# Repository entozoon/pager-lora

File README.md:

# Pager Lora

## Ingredients

- Arduino / ESP8266 ?
  Arduino is more conservative but doesn't seem to be the popular choice. I mean, speed might be an issue with transmission so bang it out on a Wemos with WIFI disabled.

## Goals

- Clamshell
- Nokia 5110 screen / e-ink
- Buzz tune on receipt
- Opening wakes up device screen
- Small as poss, but poss 18520 batteries, so..
- Lora communication over 300m

## Input

Mobile keypad text is a fun way to go. Revive that old skill.

### Drawing?

Would be nice, but bandwidth is limited, as well as rendering capabilities so.. it'd be a whole thing. Couldn't be real-time.. but still an option if I make a larger device.

## Comms

| Send Device      |       Listen Device        |        User |
| ---------------- | :------------------------: | ----------: |
| Listening always |      Listening always      |             |
|                  |                            |             |
| Emit (n?)        |                            |        Send |
|                  |          Receive           |        Buzz |
|                  |      Store to EEPROM       |             |
|                  | Emit message received? meh |             |
| Stop emitting    |                            |             |
|                  | Screen on, display message | Open device |
|                  |                            |             |

## Power

The power concerns are real. So let's make sure to do all dis:

### Disable WIFI on microcontroller

`WiFi.mode(WIFI_OFF);`

### Sleep

If possible, I mean perhaps it could sleep half the time? Let's have a shufty at some power requirements. Complete conjecture, but anyways:

- Microcontroller
  General: 20mA ESP w/out WIFI or 5mA for pro mini
  Sleep: Negligible

- LoRa (3.3v)
  Receiver: ≦ 10mA (LnaBoost off, band 1)
  Transmit: ≦ 120mA (+ 20dBm)
  Sleep: Negligible
  Total, if listening always and transmitting like 1% of the time: 11mA

- Screen
  Unlit: 1mA
  Backlit: <= 80mA, so maybe don't bother!

- 18650 2400mah 3.7v
  5v converters are supposedly 90% efficient so 2160mAh

So, assuming they're always listening and transmit at glorious 28.8kbps modem style speed now and then:

    Battery capacity (mA/h) / Current draw (mA) = hours of battery life  .. right?

    2160mAh / 32mA = 67 hours
    900mAh / 32mA = 28 hours
    240mAh / 32mA = 7.5 hours

Woah. I mean, these are conservative numbers too. Not three bad.
So yeah, sleep both chips if possible when closed and poss use an Arduino (5mA).

### C rating?

Literally anything is fine.
Peak current, with lit screen and full transmit is like 220mA, so 0.5C @ 500mA is enough. (18650 are 1C)

### Sleep LoRa chip

Just a reminder to sleep this along with the microcontroller.

## Battery

5V step ups bitch out under .5v, which won't matter much, but the efficiency varies with input voltage (and current): http://www.hobbytronics.co.uk/u1v10f5-5v-regulator

| Battery      |    V |  mAh | Effic | ->~mAh | Life(h) mAh/32mA | Notes                      |
| ------------ | ---: | ---: | ----: | -----: | ---------------: | -------------------------- |
| AAA (r/c)    | 1.5v | 1000 |  @70% |    700 |               22 |                            |
| AAA (r/c) x2 | 1.5v | 2000 |  @70% |   1400 |               44 |                            |
| AA (r/c)     | 1.5v | 2400 |  @70% |   1680 |               53 |                            |
| Lipo 50x30mm | 3.7v | 2000 |  @90% |   1800 |               56 | Better form factor than AA |
| 18650        | 3.7v | 2400 |  @90% |   2160 |               66 | All lipos easy to charge   |
| Lipo 90x60mm | 3.7v | 4000 |  @90% |   3600 |              113 | Phone bat size, affordable |

Lipo batteries supposedly self-disarge at only 5%/month (despite my experience), not far off alkaline.
So any lipo really, high mAh as possible for the best form factor.
But deeefinitely invest in a voltmeter setup (see below). Perhaps flash the screen hard and/or chirp for a turn off.

## Battery monitoring

Feed battery into analogue input, with a voltage divider to reduce it.

Wemos A0 has a voltage divider built in. 220k / 100k (2/3rdsness).
People say it has a range of 3.3V, but I should test that.

    +++++++++
        |
      [10k]
        |
        |----(100pF -> 1nF)---> analogue input
        |    reduce wobble? Didn't work..
        |
      [10k]
        |
    ---------

    V divideness = (R1 / R1 + R2)
                 = 1 / 2

So if my lipo spits out a mad 4.6V, A0 would receive 2.3V.
Update: 1024 max value is 6.1V, in reality, through my divider.

| Lipo V | Desc   | Dividered | A0 (theory) | Human  |
| ------ | ------ | --------: | ----------: | ------ |
| 4.6    | Pumped |       2.3 |         713 | 100%   |
| 4.2    | Full   |       2.1 |         652 | 100%   |
| 4      | Good   |         2 |         621 | 75%    |
| 3.86   | Mid    |      1.93 |         599 | 50%    |
| 3.75   | Low    |     1.875 |         582 | 20% !  |
| 3.7    | Low    |      1.85 |         574 | 10% !  |
| 3.5    | Dead   |      1.75 |         543 | 0% off |

    A0 (theory) = Dividered V / 3.3 * 1024

Empirical realities are close but a little different:

| Lipo V | Desc   | A0 (theory) | Human  |
| ------ | ------ | ----------: | ------ |
| 4.6    | Pumped |         762 | 100%   |
| 4.2    | Full   |         706 | 100%   |
| 4      | Good   |         660 | 75%    |
| 3.86   | Mid    |         634 | 50%    |
| 3.75   | Low    |         615 | 20% !  |
| 3.7    | Low    |         608 | 10% !  |
| 3.5    | Dead   |         577 | 0% off |

## Power off

It really should power itself off, LoRa et al, with low batt for safety. Might not be worth it though, I mean, do my charge protection circuits handle that? Probs eh?

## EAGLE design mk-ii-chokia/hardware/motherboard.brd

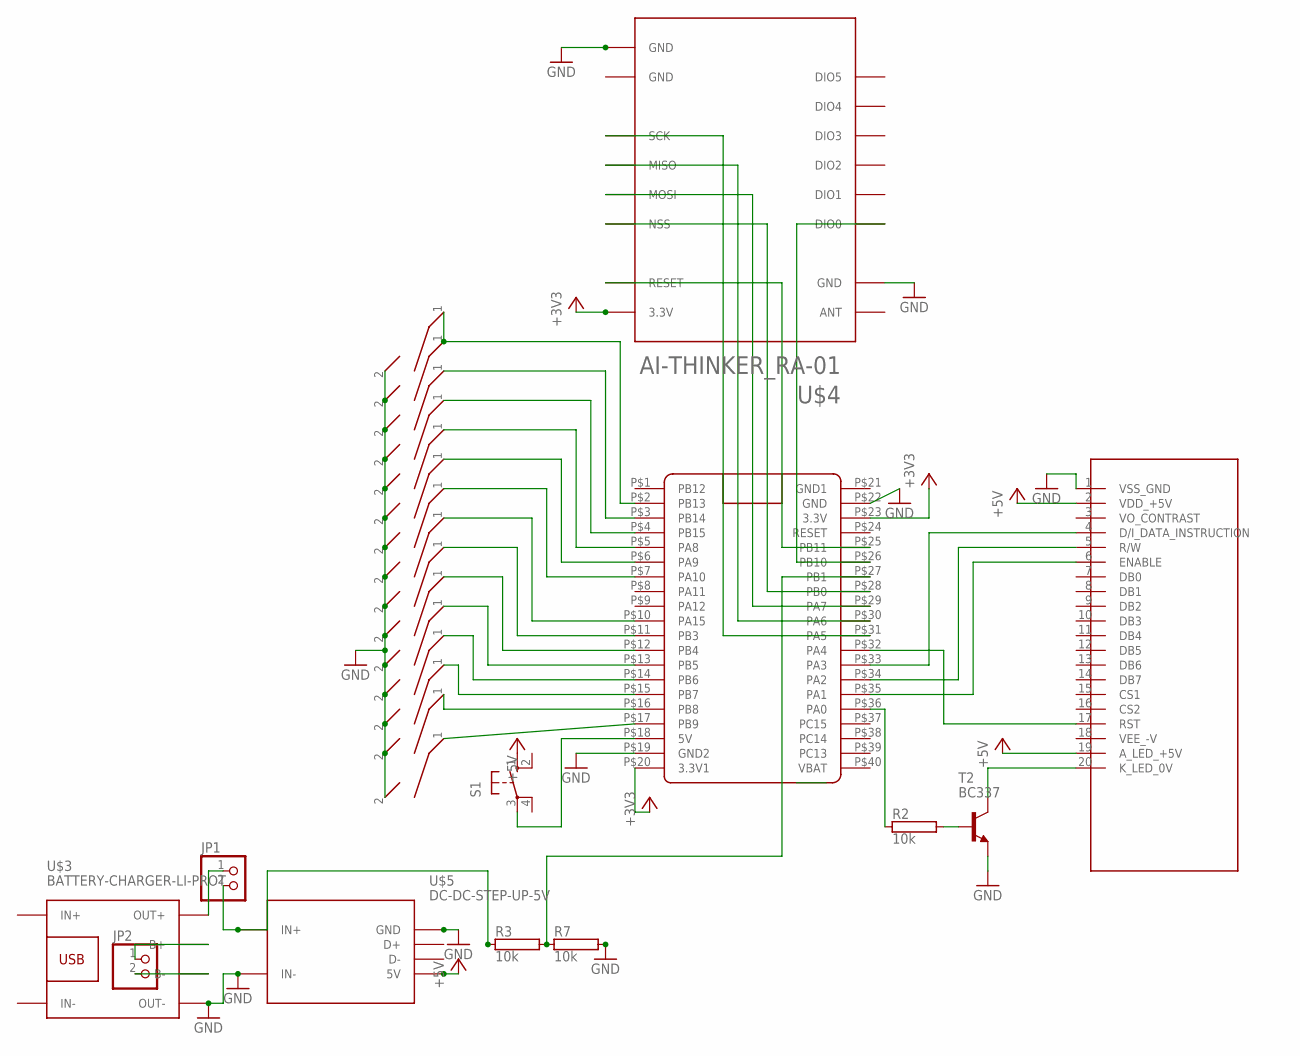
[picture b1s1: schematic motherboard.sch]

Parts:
JP1, JP2: PINHD-1X2/90; 1X02/90
R2, R3, R7: 10k; AC01
S1: 10-XX; B3F-10XX
SW1, SW2, SW3, SW4, SW5, SW6, SW7, SW8, SW9, SW10, SW11, SW12, SW13, SW14, SW15: CHERRY_MX; MX1A-XXNN
T2: BC337; TO92
U$1: W12864
U$2: BLUE_PILL
U$3: BATTERY-CHARGER-LI-PROT
U$4: AI-THINKER_RA-01
U$5: DC-DC-STEP-UP-5V

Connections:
+3V3: U$2.P$20 (3.3V1), U$2.P$23 (3.3V), U$4.P$3 (3.3V)
+5V: S1.1 (S), U$1.2 (VDD_+5V), U$1.19 (A_LED_+5V), U$5.5V
GND: R7.2, SW1.2, SW2.2, SW3.2, SW4.2, SW5.2, SW6.2, SW7.2, SW8.2, SW9.2, SW10.2, SW11.2, SW12.2, SW13.2, SW14.2, SW15.2, T2.1 (E), U$1.1 (VSS_GND), U$2.P$19 (GND2), U$2.P$22 (GND), U$3.OUT-, U$4.P$2 (GND), U$4.P$16 (GND), U$5.GND, U$5.IN-
GND1: U$2.P$21 (GND1)
unnamed: JP1.1, U$3.OUT+
unnamed: U$2.P$25 (PB11), U$4.P$4 (RESET)
unnamed: U$2.P$28 (PB0), U$4.P$15 (NSS)
unnamed: U$2.P$29 (PA7), U$4.P$14 (MOSI)
unnamed: U$2.P$30 (PA6), U$4.P$13 (MISO)
unnamed: U$2.P$31 (PA5), U$4.P$12 (SCK)
unnamed: U$2.P$26 (PB10), U$4.P$5 (DIO0)
unnamed: U$1.6 (ENABLE), U$2.P$35 (PA1)
unnamed: U$1.5 (R/W), U$2.P$34 (PA2)
unnamed: U$1.17 (RST), U$2.P$32 (PA4)
unnamed: U$1.4 (D/I_DATA_INSTRUCTION), U$2.P$33 (PA3)
unnamed: R2.2, T2.2 (B)
unnamed: T2.3 (C), U$1.20 (K_LED_0V)
unnamed: SW1.1, U$2.P$17 (PB9)
unnamed: JP1.2, R3.1, U$5.IN+
unnamed: SW2.1, U$2.P$16 (PB8)
unnamed: R2.1, U$2.P$36 (PA0)
unnamed: SW3.1, U$2.P$15 (PB7)
unnamed: SW4.1, U$2.P$14 (PB6)
unnamed: SW5.1, U$2.P$13 (PB5)
unnamed: SW6.1, U$2.P$12 (PB4)
unnamed: SW7.1, U$2.P$11 (PB3)
unnamed: R3.2, R7.1, U$2.P$27 (PB1)
unnamed: SW8.1, U$2.P$10 (PA15)
unnamed: SW9.1, U$2.P$7 (PA10)
unnamed: SW10.1, U$2.P$6 (PA9)
unnamed: SW13.1, U$2.P$3 (PB14)
unnamed: SW14.1, SW15.1, U$2.P$2 (PB13)
unnamed: SW11.1, U$2.P$5 (PA8)
unnamed: SW12.1, U$2.P$4 (PB15)
unnamed: JP2.1, U$3.B+
unnamed: JP2.2, U$3.B-
unnamed: S1.3, U$2.P$18 (5V)

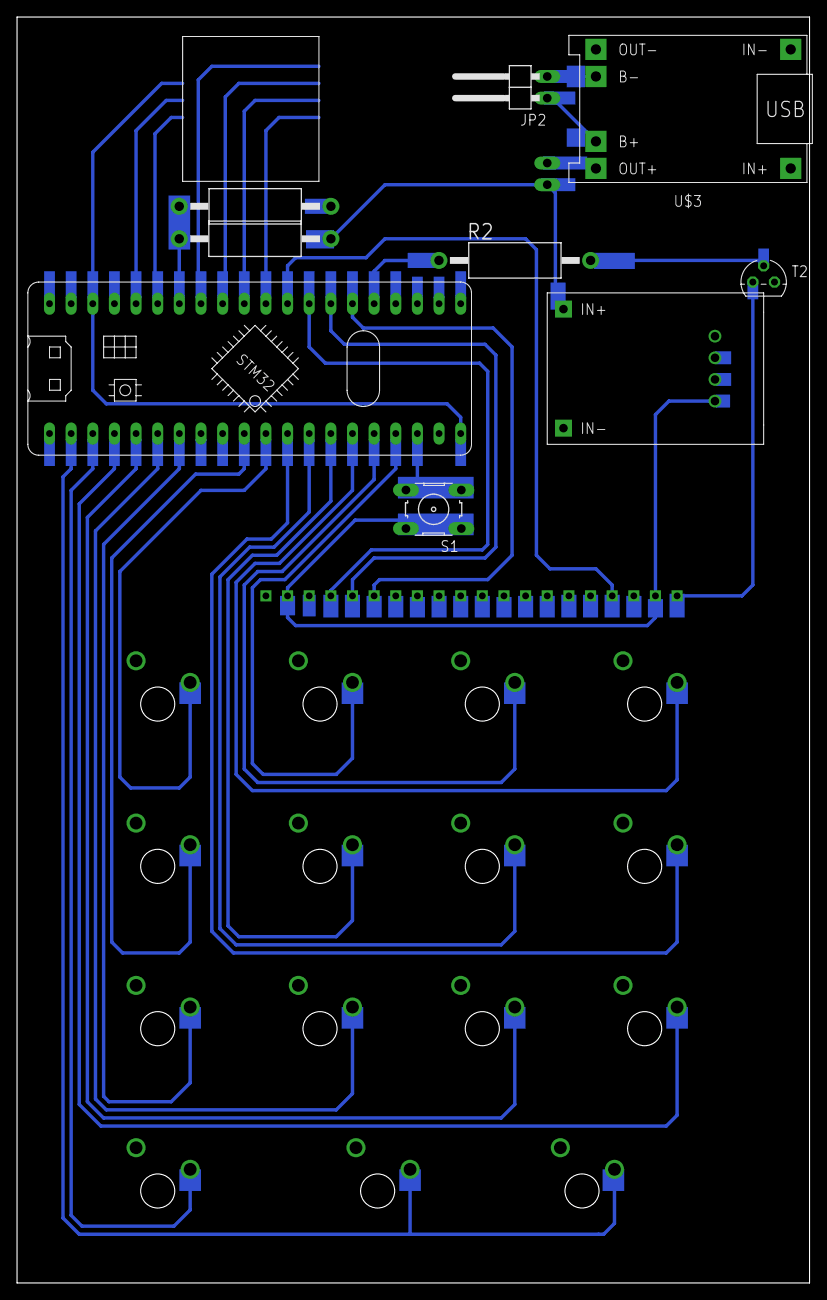
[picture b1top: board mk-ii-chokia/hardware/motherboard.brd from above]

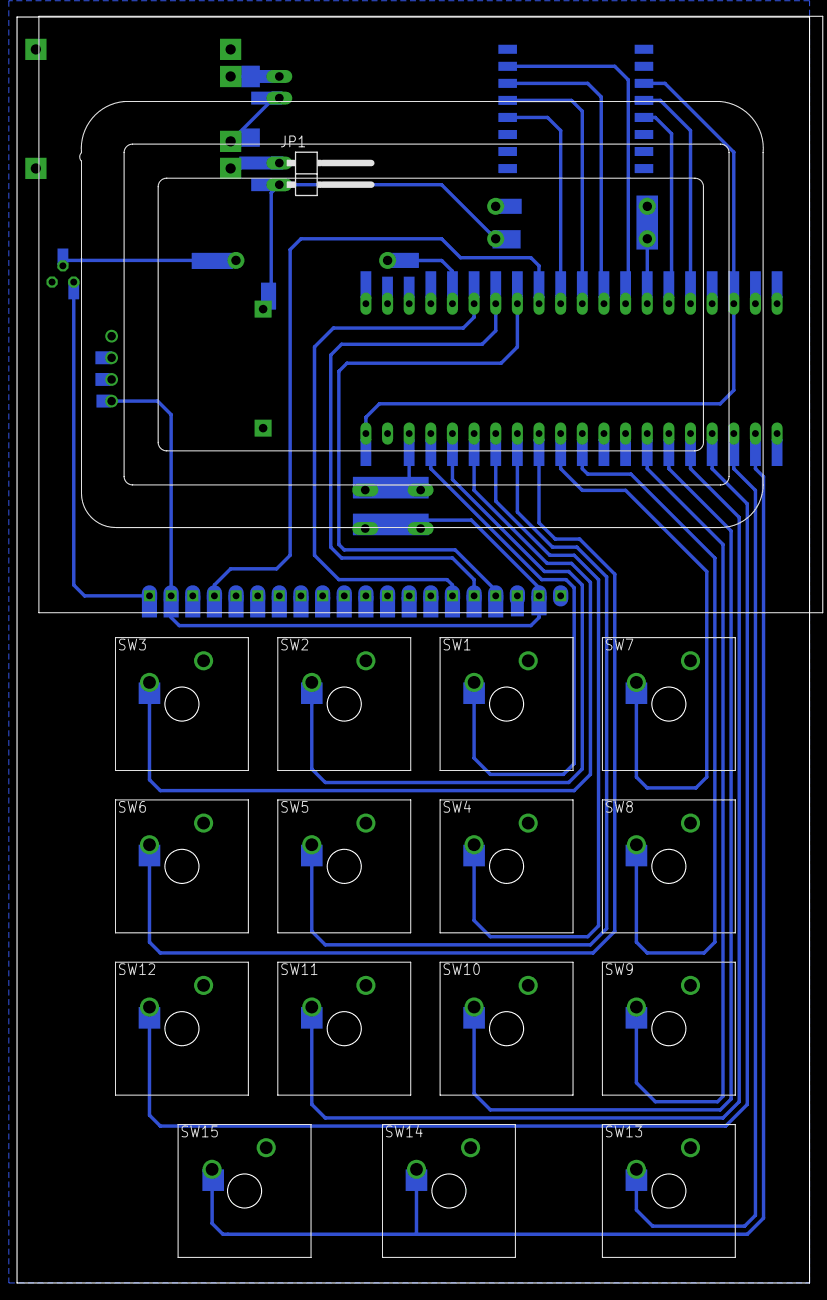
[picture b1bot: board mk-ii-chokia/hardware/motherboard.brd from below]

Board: 2 copper layers, 93.0 x 148.6 mm, 27 parts (17 on the bottom side), 36 nets.

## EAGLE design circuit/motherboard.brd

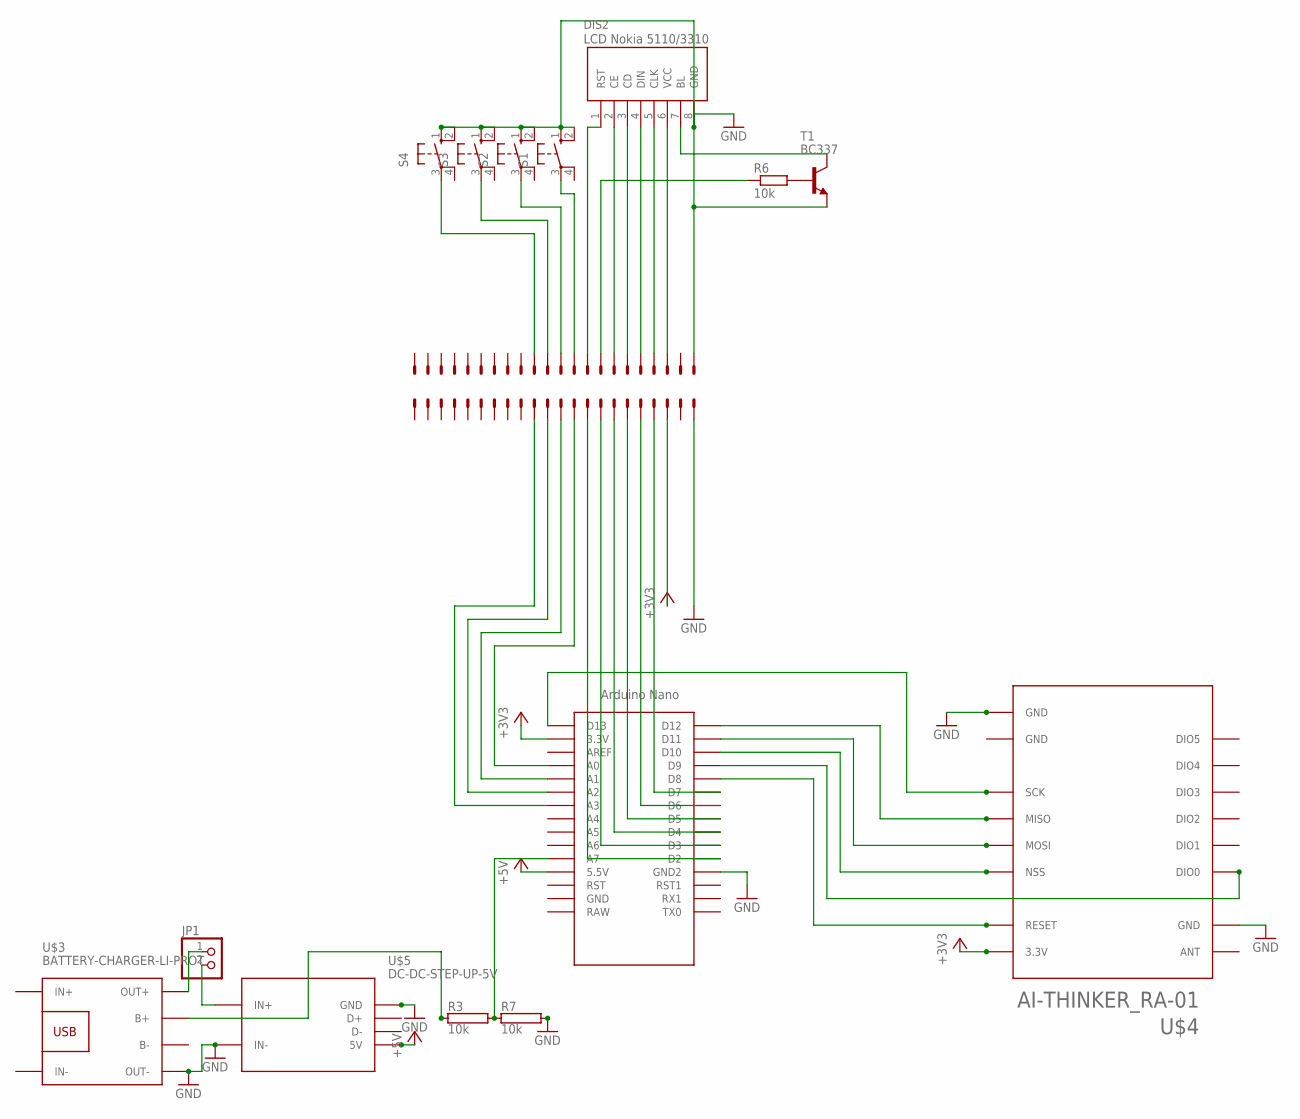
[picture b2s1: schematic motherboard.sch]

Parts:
DIS2: NOKIA5110
J1, J2: XF2L-2235-1
JP1: PINHD-1X2/90; 1X02/90
R3, R7: 10k; AC01
R6: 10k; 0204/5
S1, S2, S3, S4: 10-XX; B3F-10XX
T1: BC337; TO92
U$1: NANO
U$3: BATTERY-CHARGER-LI-PROT
U$4: AI-THINKER_RA-01
U$5: DC-DC-STEP-UP-5V

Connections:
+3V3: J1.20 (MS), U$1.3.3V, U$4.P$3 (3.3V)
+5V: U$1.5V (5.5V), U$5.5V
GND: DIS2.8 (GND), J1.22 (MS), J2.1 (MSV), R7.2, S1.1 (S), S1.2 (S1), S2.1 (S), S2.2 (S1), S3.1 (S), S3.2 (S1), S4.1 (S), S4.2 (S1), T1.1 (E), U$1.GND1 (GND2), U$3.OUT-, U$4.P$2 (GND), U$4.P$16 (GND), U$5.GND, U$5.IN-
unnamed: JP1.1, U$3.OUT+
unnamed: U$1.D13, U$4.P$12 (SCK)
unnamed: J1.19 (MS), U$1.D7
unnamed: U$1.D12, U$4.P$13 (MISO)
unnamed: U$1.D11, U$4.P$14 (MOSI)
unnamed: U$1.D10, U$4.P$15 (NSS)
unnamed: U$1.D9, U$4.P$5 (DIO0)
unnamed: U$1.D8, U$4.P$4 (RESET)
unnamed: J1.14 (MS), U$1.D2
unnamed: J1.18 (MS), U$1.D6
unnamed: J1.17 (MS), U$1.D5
unnamed: J1.16 (MS), U$1.D4
unnamed: J1.15 (MS), U$1.D3
unnamed: R6.2, T1.2 (B)
unnamed: JP1.2, U$5.IN+
unnamed: R3.1, U$3.B+
unnamed: DIS2.1 (RST), J2.9 (MS)
unnamed: J2.8 (MS), R6.1
unnamed: J2.10 (MS), S1.3
unnamed: J2.11 (MS), S2.3
unnamed: J2.12 (MS), S3.3
unnamed: DIS2.7 (BL), T1.3 (C)
unnamed: R3.2, R7.1, U$1.A7
unnamed: DIS2.6 (VCC), J2.3 (MS)
unnamed: DIS2.5 (CLK), J2.4 (MS)
unnamed: DIS2.4 (DIN), J2.5 (MS)
unnamed: DIS2.3 (CD), J2.6 (MS)
unnamed: DIS2.2 (CE), J2.7 (MS)
unnamed: J2.13 (MS), S4.3
unnamed: J1.13 (MS), U$1.A0
unnamed: J1.12 (MS), U$1.A1
unnamed: J1.11 (MS), U$1.A2
unnamed: J1.10 (MS), U$1.A3

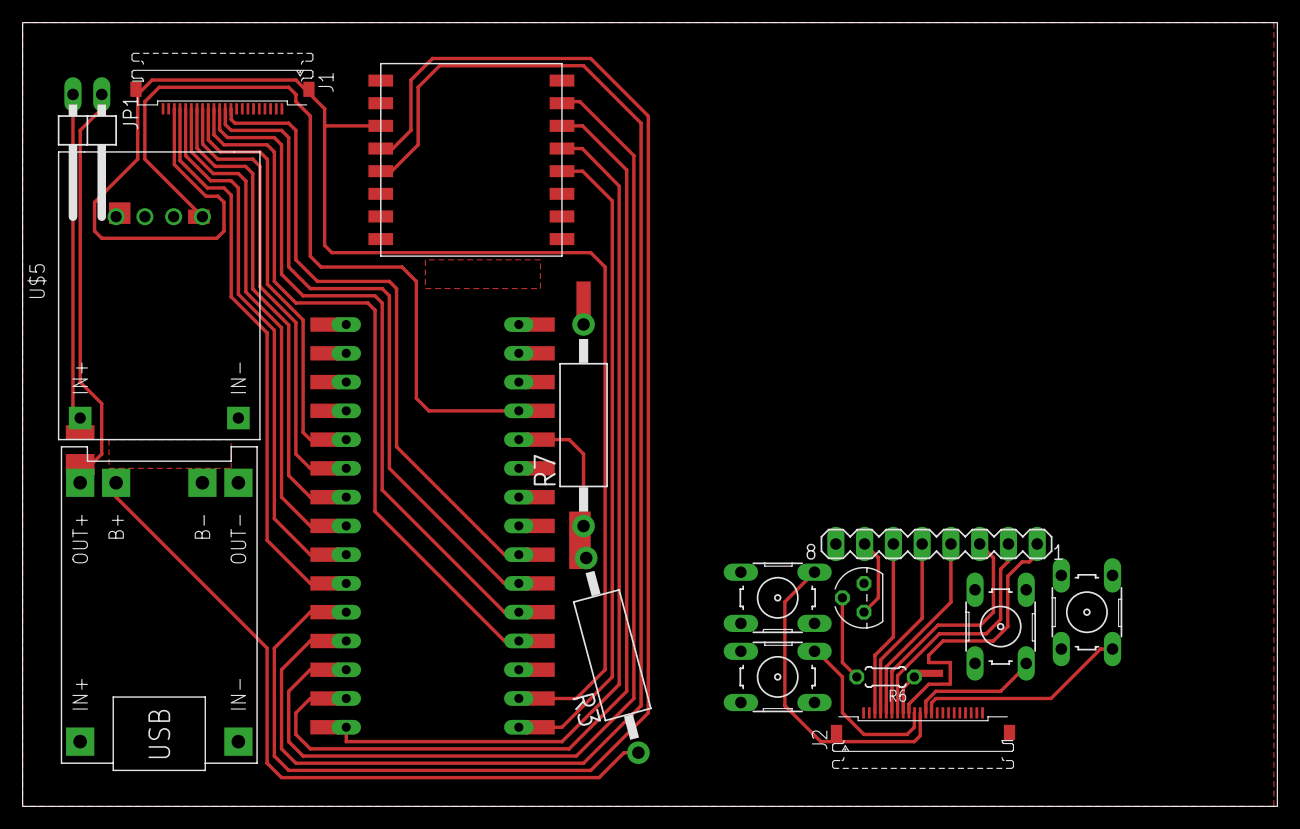
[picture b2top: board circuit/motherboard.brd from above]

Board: 2 copper layers, 110.8 x 69.2 mm, 16 parts (0 on the bottom side), 36 nets.

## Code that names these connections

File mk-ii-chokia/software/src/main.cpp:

#include <Arduino.h>
#include <U8g2lib.h>
#include <SPI.h>
#include <Wire.h>

// //
// // BLINK
// //
// void setup()
// {
//   pinMode(LED_BUILTIN, OUTPUT);
// }
// void loop()
// {
//   digitalWrite(LED_BUILTIN, HIGH); // turn the LED on (HIGH is the voltage level)
//   delay(200);                      // wait for a second
//   digitalWrite(LED_BUILTIN, LOW);  // turn the LED off by making the voltage LOW
//   delay(200);                      // wait for a second
// }

//
// LCD Test
//
U8G2_ST7920_128X64_1_SW_SPI u8g2(
    U8G2_R0, // rotation
    PA1,     // Clock "E" enable?
    PA2,     // Data "R/W" might have this and next wrong way.. but meh
    PA3,     // CS "RS" "D"
    PA4      // Reset "RST"
);
// Also connect +5v to VCC, BLA
// and - to GND, PSB, BLK
void setup(void)
{
  delay(10000);         // ALWAYS delay or it can't be reprogrammed easily. Press reset during build
  pinMode(PA0, OUTPUT); // dim
  u8g2.begin();
}
void loop(void)
{
  analogWrite(PA0, 255);
  u8g2.firstPage();
  do
  {
    // https://github.com/olikraus/u8g2/wiki/u8g2reference
    u8g2.setFont(u8g2_font_ncenB14_tr);
    u8g2.drawStr(0, 24, "Hello World!");
    // Can't bleeding get it to output a random string
    // char alphabet[] = {"ABCDEFGHIJKLMNOPQRSTUVWXYZ"};
    // char char_array[] = {""};
    // char_array[0] = char(random(0, 9));
    // // strcpy(char_array, alphabet[random(0, 25)].c_str());
    // u8g2.drawStr(40, 50, char_array);
    u8g2.drawBox(random(0, 100), random(30, 50), 8, 8);
    // Not amazing, then again I've no idea what the page system is so..
  } while (u8g2.nextPage());
}

// //
// // Backlight dimming test
// //
// void setup()
// {
//   Serial.begin(9600);
//   delay(10000); // ALWAYS delay or it can't be reprogrammed easily. Press reset during build
//   pinMode(PA0, OUTPUT);
// }
// float x = 0;
// float pi = 3.141592;
// void loop()
// {
//   // if (x > 255)
//   //   x = 0;
//   // Serial.print(x);
//   // Serial.print(' ');
//   // analogWrite(9, x);
//   // delay(20);
//   // x++;
//   if (x > 4 * pi)
//     x = 0;
//   int y = floor(255 * ((sin(x / 2 - pi / 2)) / 2 + .5));
//   // Serial.print(y);
//   // Serial.print(' ');
//   analogWrite(PA0, y);
//   x += 0.01;
//   delay(5);
// }

// //
// // RECEIVE
// //
// #include <SPI.h>
// #include <LoRa.h>
// void setup()
// {
//   Serial.begin(9600);
//   delay(10000); // for uploading to device
//   Serial.println("\nLoRa Receiver");
//   //          (nss, reset, dio0); (dio0 unused)
//   // LoRa.setPins(10, 9);
//   LoRa.setPins(PB0, PB11); //, PB10);  // only sending..
//   if (!LoRa.begin(433E6)) // 433 is legal in the UK and capable by device. 863-870 otherwise. worried it'll clash though
//   {
//     Serial.println("Starting LoRa failed!");
//     while (1)
//       ;
//   }
// }
// void loop()
// {
//   // try to parse packet
//   int packetSize = LoRa.parsePacket();
//   if (packetSize)
//   {
//     // received a packet
//     Serial.print("Received packet '");
//     // read packet
//     while (LoRa.available())
//     {
//       Serial.print((char)LoRa.read());
//     }
//     // print RSSI of packet
//     Serial.print("' with RSSI "); // Received Signal Strength Indicator (0 is theoretical full strength)
//     Serial.println(LoRa.packetRssi());
//   }
// }

// //
// // SEND
// //
// #include <SPI.h>
// #include <LoRa.h>
// int counter = 0;
// void setup()
// {
//   delay(10000); // for uploading to device
//   Serial.begin(9600);
//   Serial.println("\nLoRa Sender");
//   //          (nss, reset, dio0); (dio0 unused)
//   LoRa.setPins(PB0, PB11); //, PB10);  // only sending..
//   if (!LoRa.begin(433E6)) // 433 is legal in the UK and capable by device. 863-870 otherwise. worried it'll clash though
//   {
//     Serial.println("Starting LoRa failed!");
//     while (1)
//       ;
//   }
// }
// void loop()
// {
//   Serial.print("Sending packet: ");
//   Serial.println(counter);
//   // send packet
//   LoRa.beginPacket();
//   LoRa.print("hey from chokia ");
//   LoRa.print(counter);
//   LoRa.endPacket();
//   counter++;
//   delay(1000);
// }

// //
// // SENDY RECEIVY
// //
// #include <SPI.h>
// #include <LoRa.h>
// long counter = 0;
// long ticker = 0;
// long tickerSnapshot = 0;
// void setup()
// {
//   delay(15000); // for uploading to device
//   Serial.begin(9600);
//   Serial.println("\nLoRa Receiver");
//   //          (nss, reset, dio0); (dio0 unused)
//   // LoRa.setPins(PB0, PB1); //, PA4); // only sending..
//   LoRa.setPins(PB0, PB11); //, PB10);  // only sending..
//   if (!LoRa.begin(433E6))  // 433 is legal in the UK and capable by device. 863-870 otherwise. worried it'll clash though
//   {
//     Serial.println("Starting LoRa failed!");
//     while (1)
//       ;
//   }
// }
// void loop()
// {
//   // try to parse packet
//   int packetSize = LoRa.parsePacket();
//   if (packetSize)
//   {
//     // received a packet
//     Serial.print("Received: '");
//     // read packet
//     while (LoRa.available())
//     {
//       Serial.print((char)LoRa.read());
//     }
//     // print RSSI of packet
//     Serial.print("' with RSSI "); // Received Signal Strength Indicator (0 is theoretical full strength)
//     Serial.println(LoRa.packetRssi());
//     // delay(10);
//   }

//   if (ticker > 5000)
//   {
//     tickerSnapshot = millis();
//     Serial.print("Sending: ");
//     Serial.println(counter);
//     // send packet
//     LoRa.beginPacket();
//     LoRa.print("Hey from chokia ");
//     LoRa.print(counter);
//     LoRa.endPacket();
//     counter++;
//     // delay(10);
//   }
//   ticker = millis() - tickerSnapshot;
// }

//
// Button test
// (Complete garbage of course. Need to properly key scan, I think?)
//
// void setup()
// {
//   delay(10000);
//   Serial.begin(9600);
//   pinMode(PB9, INPUT_PULLUP);
//   pinMode(PB8, INPUT_PULLUP);
//   pinMode(PB7, INPUT_PULLUP);
//   pinMode(PB6, INPUT_PULLUP);
//   pinMode(PB5, INPUT_PULLUP);
//   pinMode(PB4, INPUT_PULLUP);
//   pinMode(PB3, INPUT_PULLUP);
//   pinMode(PA15, INPUT_PULLUP);
//   // PA11
//   // PA12 explode it (USB)
//   pinMode(PA10, INPUT_PULLUP);
//   pinMode(PA9, INPUT_PULLUP);
//   pinMode(PA8, INPUT_PULLUP);
//   pinMode(PB15, INPUT_PULLUP);
//   pinMode(PB14, INPUT_PULLUP);
//   pinMode(PB13, INPUT_PULLUP);
//   pinMode(PB12, INPUT_PULLUP);
// }
// void loop()
// {
//   if (digitalRead(PB9) == 0)
//   {
//     Serial.println("PB9");
//   }
//   if (digitalRead(PB8) == 0)
//   {
//     Serial.println("PB8");
//   }
//   if (digitalRead(PB7) == 0)
//   {
//     Serial.println("PB7");
//   }
//   if (digitalRead(PB6) == 0)
//   {
//     Serial.println("PB6");
//   }
//   if (digitalRead(PB5) == 0)
//   {
//     Serial.println("PB5");
//   }
//   if (digitalRead(PB4) == 0)
//   {
//     Serial.println("PB4");
//   }
//   if (digitalRead(PB3) == 0)
//   {
//     Serial.println("PB3");
//   }
//   if (digitalRead(PA15) == 0)
//   {
//     Serial.println("PA15");
//   }
//   if (digitalRead(PA10) == 0)
//   {
//     Serial.println("PA10");
//   }
//   if (digitalRead(PA9) == 0)
//   {
//     Serial.println("PA9");
//   }
//   if (digitalRead(PA8) == 0)
//   {
//     Serial.println("PA8");
//   }
//   if (digitalRead(PB15) == 0)
//   {
//     Serial.println("PB15");
//   }
//   if (digitalRead(PB14) == 0)
//   {
//     Serial.println("PB14");
//   }
//   if (digitalRead(PB13) == 0)
//   {
//     Serial.println("PB13");
//   }
//   if (digitalRead(PB12) == 0)
//   {
//     Serial.println("PB12");
//   }
// }

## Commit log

2019-12-02 Thinkings
2019-12-02 Maths
2019-12-02 Thoughts
2019-12-13 Worked out the whole battery theory lolol
2019-12-13 Safety
2020-02-27 Tried to get arduino-lmic going, and it seems to be.. but nothing receiving
2020-02-27 It works! Sending and receiving!! with a range of like.. 10cm though
2020-02-27 Voltmeter circuitry and RL values
2020-02-28 Battery figurings
2020-03-01 Building circuit, w/ Arduino Nano
2020-03-02 Totally managed to create a glyph graphic font version of original Nokia style!
2020-03-03 Think I've got the circuitry down, boarding next
2020-03-04 PCB coming along nicely
2020-03-04 Finished the PCB.. and then decided I should split the display/buttons separately
2020-03-05 Getting to be quite a serious design..
2020-03-06 Library parts are annoying
2020-03-06 Motherboard complete!
2020-03-06 Okay _now_ I'm happy with the motherboard
2020-03-07 Real life is gritty! - Etching at this point
2020-03-11 Jank
2020-03-23 Re-organising for Chokia mk II
2020-03-23 Chokia platformio - STM32
2020-03-23 Ganking together libs for chonky serial display
2020-03-23 Happy with that as an LCD test
2020-03-23 They're backup files! Argh
2020-03-23 Removing backups from repo
2020-03-24 Chokia sends. Pager receives. Not vice-versa...
2020-03-24 Parity
2020-03-24 I think it _is_ working, just.. serially fucked
2020-03-24 Twonk
2020-03-24 Nano debug
2020-03-24 I think the lora packet send is blocking, and they're overlapping on boot
2020-03-24 Unless endpacket kills it
2020-03-24 Pin mistake? was that all it was?
2020-03-24 THEY'RE TALKING!
2020-03-24 Eagle grief and keycaps
2020-03-26 PCB trackin'
2020-03-26 Ready 2 etch dot com?
2020-07-29 dump

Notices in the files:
parts and their libraries:
diy-modules: Released under the Creative Commons Attribution 4.0 International License: http://creativecommons.org/licenses/by/4.0
